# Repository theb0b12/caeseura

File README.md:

# Caeseura

**cae·sue·ra**
/siːˈzʊrə/

**noun**

1. in modern prosody : a usually rhetorical break in the flow of sound in the middle of a line of verse
2. break, interruption
   > "a *caesura* between the movie and its sequel"
3. a pause marking a rhythmic point of division in a melody

[credit](https://www.merriam-webster.com/dictionary/caesura)

***etymology***

Altered spelling of *caesura*, intentionally adding the **e** as wordplay, referencing the spelling of the city of **Céüse** in France, a very cool sport climbing destination and host to some of the hardest routes in the world. The sword **Caesura** from *The Kingkiller Chronicle*, great book btw. And the concept of splitting or dividing (get it, split keebs).

---

## Photos

|  |  |
| :------------------------------------------: | :------------------------------------------: |
|  |  |

---

## Builds

<p float="left">
  
  <div align="center">
    
  </div>
</p>

Lu's Build, with a custom case and nice Asymplex/3D-printed Subliminal Contraction keycaps

---

My Build, with a custom display cover and nice MOA keycaps

## Features

- **47 keys**
- **Row Staggered**
- **Split design**
- **MX & Choc compatible** - hotswap sockets, choc v1 and v2 (if you snip the extra pin)
- **Wireless** - powered by the [nice!nano v2](https://nicekeyboards.com/nice-nano/) and [ZMK firmware](https://zmk.dev/)
- **Open source** - PCB gerbers + kicad files, case files, ZMK config, and Ergogen YAML

---

## Bill of Materials (BOM)

These are the things from my build. In hindsight I would've changed some things, use it with a couple more than a few grains of salt. Total cost will vary depending on switch choice, shipping, and discounts.

| Item                                 | Qty     | Unit Price | Total   | Link                                                                                                                |
| ------------------------------------ | ------- | ---------- | ------- | ------------------------------------------------------------------------------------------------------------------- |
| nice!nano v2                         | 2       | $25.00     | $50.00  | [Typeractive](https://typeractive.xyz/products/nice-nano)                                                           |
| Batteries                            | 1 set   | $15.49     | $15.49  | [Amazon](https://www.amazon.com/dp/B09726K2LC)                                                                      |
| PCB (left + right)                   | 1 set   | $27.00     | $27.00  | JLCPCB                                                                                                              |
| Switches (Choc)                      | ~47     | -          | -       | personal choice                                                                                                     |
| Choc hotswap sockets (x10)           | 5 packs | $1.50      | $7.50   | [Typeractive](https://typeractive.xyz/products/hotswap-sockets?variant=45742200324327)                              |
| MX hotswap sockets                   | 5 packs | $1.50      | $7.50   | [Typeractive](https://typeractive.xyz/products/hotswap-sockets?variant=45742200291559)                              |
| Reset switch (Panasonic EVQ-PUA02K)  | 3       | $0.67      | $2.01   | [Digikey](https://www.digikey.com/en/products/detail/panasonic-electronic-components/EVQ-PUA02K/286334)             |
| Power switch (SMD)                   | 2 packs | $1.50      | $3.00   | [Typeractive](https://typeractive.xyz/products/power-switch)                                                        |
| JST PH 2-pin battery connector       | 2       | $0.10      | $0.20   | [Digikey](https://www.digikey.com/en/products/detail/jst-sales-america-inc/S2B-PH-K-S/926626)                       |
| Keycaps                              | ~47     | -          | -       | personal choice                                                                                                     |
| SOD-123 diodes (1N4148W)             | 50      | $0.0495    | $2.48   | [Digikey](https://www.digikey.com/en/products/detail/diotec-semiconductor/1N4148W/18833653)                         |
| Mill-Max 310 board sockets           | 6       | $1.43      | $8.58   | [Digikey](https://www.digikey.com/en/products/detail/mill-max-manufacturing-corp/310-47-112-41-001000/7364039)      |
| Mill-Max 3320 pins                   | 65      | $0.0876    | $5.69   | [Digikey](https://www.digikey.com/en/products/detail/mill-max-manufacturing-corp/3320-0-00-15-00-00-03-0/4147392)   |
| Adhesive rubber feet                 | 1 pack  | $6.99      | $6.99   | [Amazon](https://www.amazon.com/dp/B0DXH5D1FQ)                                                                      |
| M2x6mm FHCS screws                   | 1 pack  | $8.69      | $8.69   | [Amazon](https://www.amazon.com/dp/B01MYRN6A1)                                                                      |
| M2 heat-set inserts                  | 1 pack  | $6.99      | $6.99   | [Amazon](https://www.amazon.com/dp/B0FJXLNMLM)                                                                      |

---

## Build Guide

WIP

---

## Credits

### Designer

Built and designed by **[@theb0b12](https://github.com/theb0b12)**.

### Special Thanks

A massive shout-out to **[@stardustArc](https://github.com/stardustArc)** - she essentially walked me through the entire design and build process step by step. This keyboard would not exist without her help.

Big thanks to **[@zakwaykway](https://github.com/zakwaykway)** for their knowledge about switches and switch footprints, invaluable when figuring out the dual MX/Choc hotswap setup.

Shout-out to the **[Ergogen Discord](https://discord.com/invite/DbCfZfZ)** and the **[ZMK Discord](https://discord.com/invite/sycytVQ)** communities, the collective knowledge in both servers made this project possible.

Thanks to **[@genteure](https://github.com/genteure)** for his help with the board shield and his excellent tool **[ZMK Shield Wizard](https://shield-wizard.genteure.workers.dev/)**, which makes setting up custom ZMK shields dramatically easier.

### Tools & Stuff

- **[Ergogen](https://ergogen.xyz/)**
- **[ceoloide footprint library](https://github.com/ceoloide/ergogen-footprints)**
- **[ZMK Firmware](https://zmk.dev/)**
- **[nice!nano](https://nicekeyboards.com/nice-nano/)**
- **[ZMK Shield Wizard](https://shield-wizard.genteure.workers.dev/)**
- **[Keymap Layout Tools](https://nickcoutsos.github.io/keymap-layout-tools/)**
- **[Keymap Editor](https://nickcoutsos.github.io/keymap-editor/)**

---

## License

This project is open source with the AGPLv3 license. PCB design files, case files, and ZMK config are free to use, modify, and build from. If you make changes and share them, a link back here would be appreciated.

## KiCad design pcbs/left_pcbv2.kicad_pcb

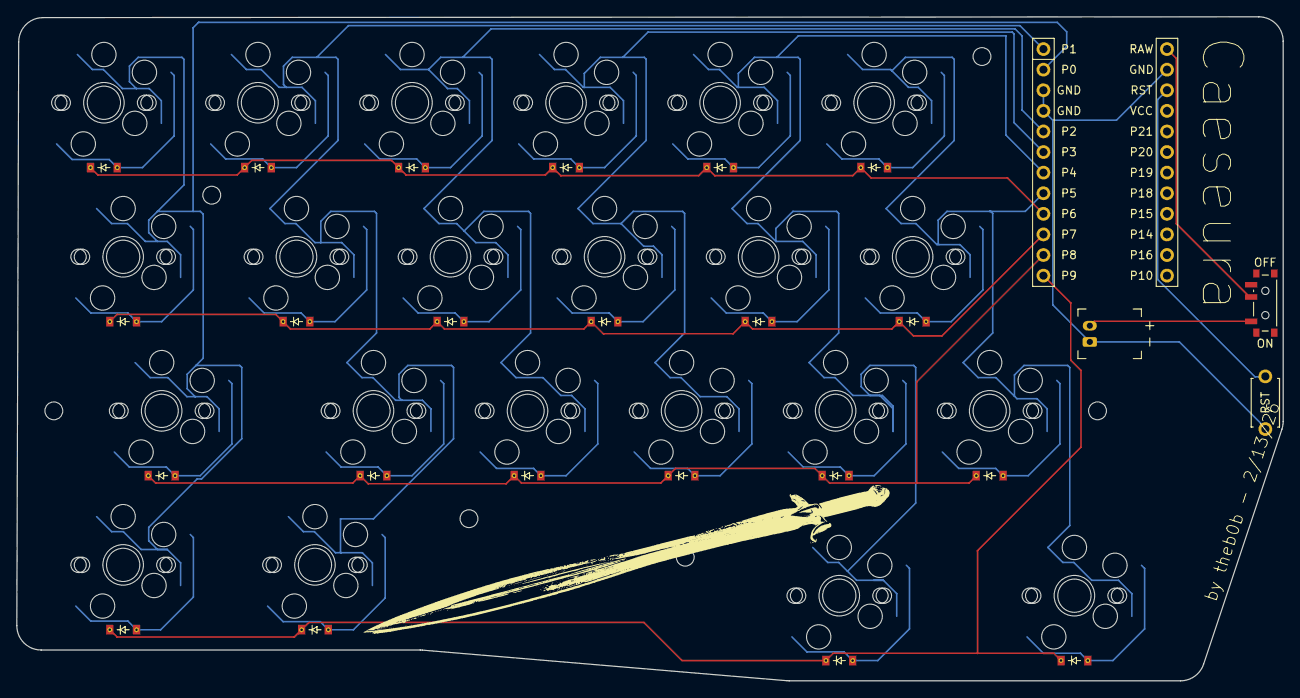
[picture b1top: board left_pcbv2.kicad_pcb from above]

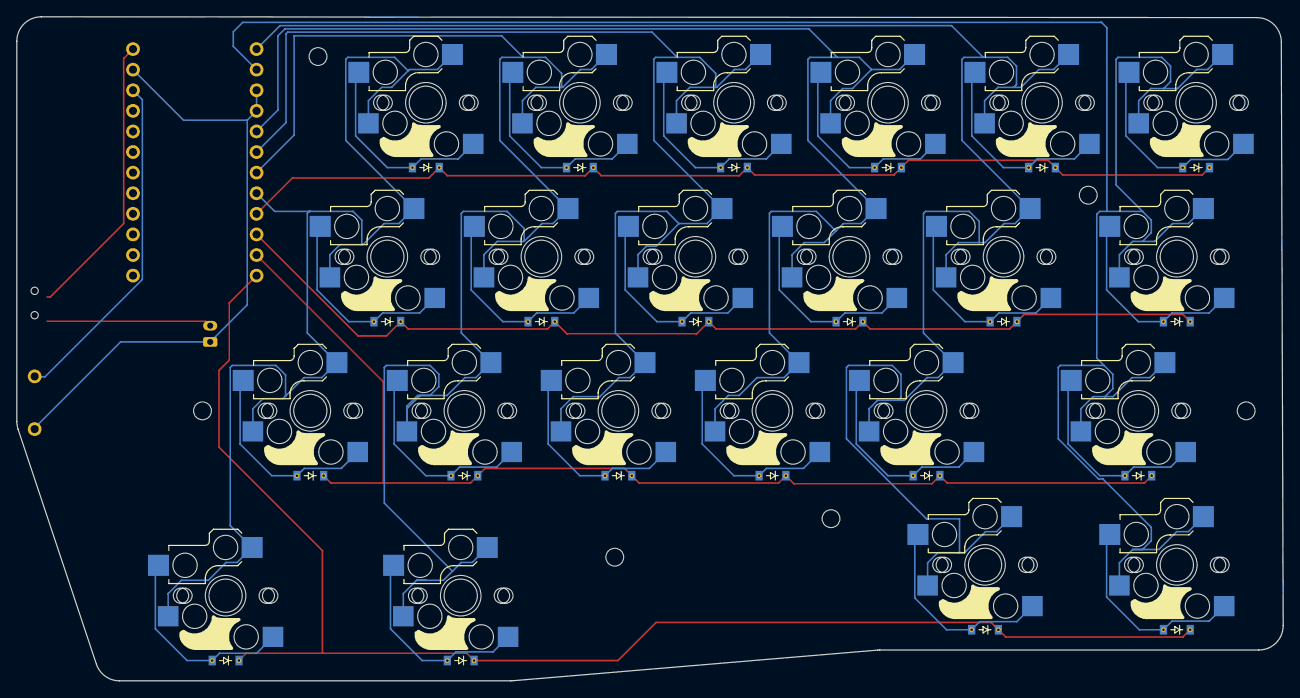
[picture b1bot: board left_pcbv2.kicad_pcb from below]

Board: 2 copper layers, 156.2 x 81.9 mm, 76 parts (44 on the bottom side), 36 nets.

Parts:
D1, D2, D3, D4, D5, D6, D7, D8, D9, D10, D11, D12, D13, D14, D15, D16, D17, D18, D19, D20, D21, D22: ComboDiode
JST1: battery_connector_jst_ph_2
MCU1: mcu_nice_nano
MH1, MH2, MH3, MH4, MH5, MH6: mounting_hole_npth
PWR1: power_switch_smd_side
RST1: reset_switch_tht_top
S1, S2, S3, S4, S5, S6, S7, S8, S9, S10, S11, S12, S13, S14, S15, S16, S17, S18, S19, S20, S21, S22: switch_choc_v1_v2
S23, S24, S25, S26, S27, S28, S29, S30, S31, S32, S33, S34, S35, S36, S37, S38, S39, S40, S41, S42, S43, S44: switch_mx

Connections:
BAT_P: JST1.2, PWR1.1
GND: JST1.1, MCU1.2, MCU1.21, MCU1.22, RST1.2
P0: MCU1.23, S1.1, S7.1, S13.1, S19.1, S23.1, S29.1, S35.1, S41.1
P1: MCU1.24, S2.1, S8.1, S14.1, S20.1, S24.1, S30.1, S36.1, S42.1
P2: MCU1.20, S3.1, S9.1, S15.1, S25.1, S31.1, S37.1
P3: MCU1.19, S4.1, S10.1, S16.1, S26.1, S32.1, S38.1
P4: MCU1.18, S5.1, S11.1, S17.1, S21.1, S27.1, S33.1, S39.1, S43.1
P5: MCU1.17, S6.1, S12.1, S18.1, S22.1, S28.1, S34.1, S40.1, S44.1
P6: D1.1, D2.1, D3.1, D4.1, D5.1, D6.1, MCU1.16
P7: D7.1, D8.1, D9.1, D10.1, D11.1, D12.1, MCU1.15
P8: D13.1, D14.1, D15.1, D16.1, D17.1, D18.1, MCU1.14
P9: D19.1, D20.1, D21.1, D22.1, MCU1.13
RAW: MCU1.1, PWR1.2
RST: MCU1.3, RST1.1
a_default: D8.1, D8.2, S8.2, S30.2
b_default: D18.1, D18.2, S18.2, S40.2
c_default: D16.1, D16.2, S16.2, S38.2
d_default: D10.1, D10.2, S10.2, S32.2
e_default: D4.1, D4.2, S4.2, S26.2
esc_default: D1.1, D1.2, S1.2, S23.2
f_default: D11.1, D11.2, S11.2, S33.2
g_default: D12.1, D12.2, S12.2, S34.2
lctrl_default: D19.1, D19.2, S19.2, S41.2
lower_default: D21.1, D21.2, S21.2, S43.2
lshift_default: D13.1, D13.2, S13.2, S35.2
q_default: D2.1, D2.2, S2.2, S24.2
r_default: D5.1, D5.2, S5.2, S27.2
s_default: D9.1, D9.2, S9.2, S31.2
space_default: D22.1, D22.2, S22.2, S44.2
super_default: D20.1, D20.2, S20.2, S42.2
t_default: D6.1, D6.2, S6.2, S28.2
tab_default: D7.1, D7.2, S7.2, S29.2
v_default: D17.1, D17.2, S17.2, S39.2
w_default: D3.1, D3.2, S3.2, S25.2
x_default: D15.1, D15.2, S15.2, S37.2
z_default: D14.1, D14.2, S14.2, S36.2

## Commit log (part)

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2026-03-13 added README
2026-03-13 added to README
2026-03-13 did this change anything
2026-03-13 first draft of README
2026-03-13 2nd draft
2026-03-13 convert zmk-config from submodule to regular folder
2026-03-13 added smth stuff idk
2026-03-13 added wip stuff
2026-03-13 added some things
2026-03-13 changed links
2026-03-14 Fix Discord username formatting for stardustArc
    Corrected Discord username formatting for stardustArc.
2026-03-14 Update battery item description in README
2026-03-15 test
2026-03-15 test2
2026-03-15 changes v2
2026-04-30 Refine feature descriptions in README.md
    Updated descriptions for compatibility, case, and reset button features.
2026-04-30 Add MIT License to the project
2026-04-30 Specify MIT license in README
2026-05-01 fixed the bodge
2026-05-05 updated README with photos
2026-05-05 Fix capitalization in build description
2026-05-24 updated pcb and changed photos
